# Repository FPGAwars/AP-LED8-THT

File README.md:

# AP-LED8-THT
Alhambra Peripheral board with 8 through-hole LEDs

It is a tiny board with eight 3mm though-hole LEDs for connecting to the Alhambra-II FPGA board.  
This board is also used as a reference for teaching students how to design their first PCB (so, it is a kind of "hello world" hardware)

## Connection to Alhambra II Board

## Certification mark

This board is Opensource hardware, certified by the [OSHWA](https://www.oshwa.org/)

* Certification ID: [ES000043](https://certification.oshwa.org/es000043.html)  

* Certification mark:

## License

Documentation licensed under the [Creative Commons Attribution Share Alike 4.0 International License](https://creativecommons.org/licenses/by-sa/4.0/)

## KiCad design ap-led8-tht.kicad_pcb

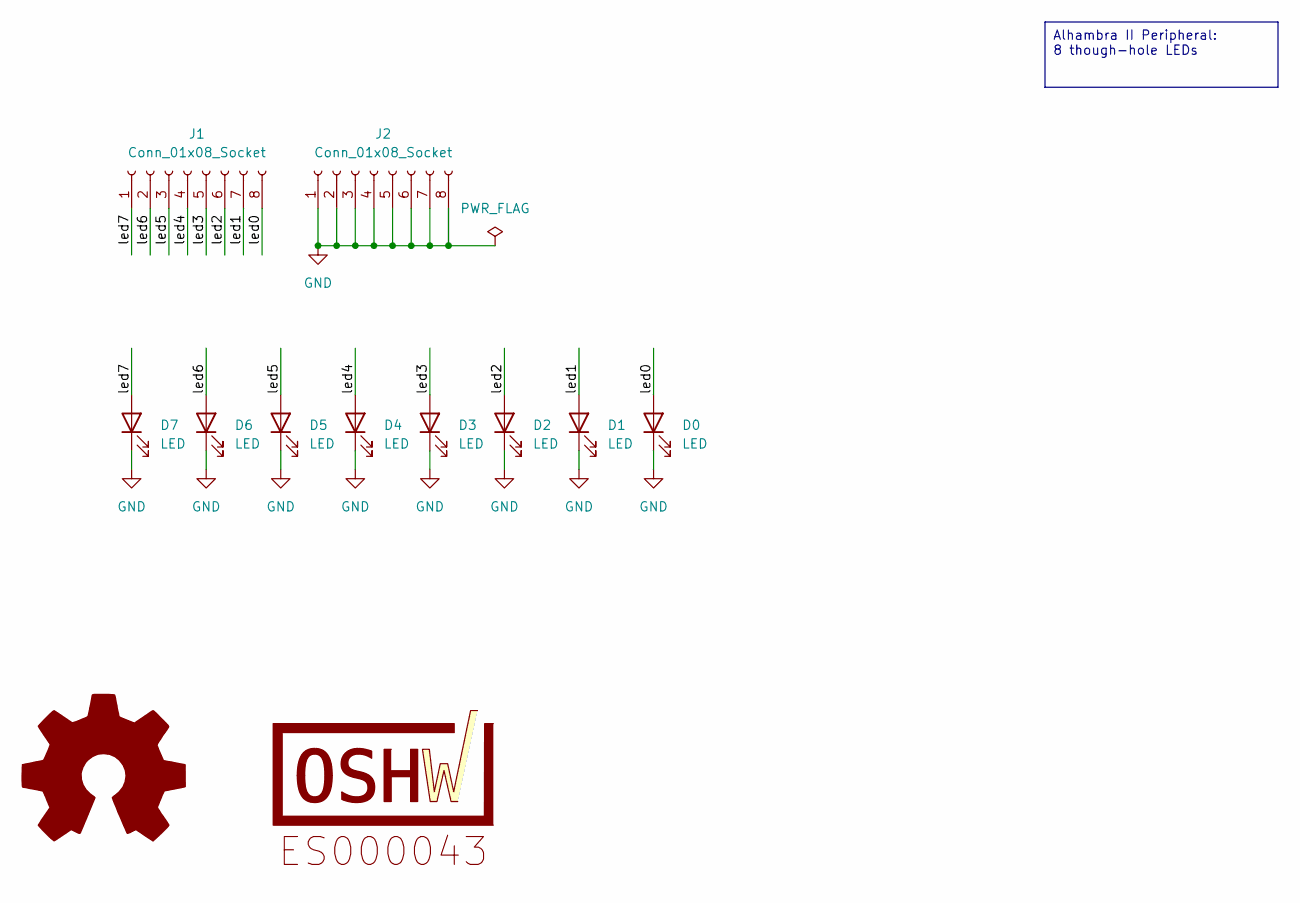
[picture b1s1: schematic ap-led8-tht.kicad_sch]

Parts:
D0, D1, D2, D3, D4, D5, D6, D7: LED; LED_THT__LED_D3.0mm
J1, J2: Conn_01x08_Socket; PinSocket_1x08_P2.54mm_Vertical
LOGO2: (no value)

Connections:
/led0: D0.2 (A), J1.8
/led1: D1.2 (A), J1.7
/led2: D2.2 (A), J1.6
/led3: D3.2 (A), J1.5
/led4: D4.2 (A), J1.4
/led5: D5.2 (A), J1.3
/led6: D6.2 (A), J1.2
/led7: D7.2 (A), J1.1
GND: D0.1 (K), D1.1 (K), D2.1 (K), D3.1 (K), D4.1 (K), D5.1 (K), D6.1 (K), D7.1 (K), J2.1, J2.2, J2.3, J2.4, J2.5, J2.6, J2.7, J2.8

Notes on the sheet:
Alhambra II Peripheral: 8 though-hole LEDs

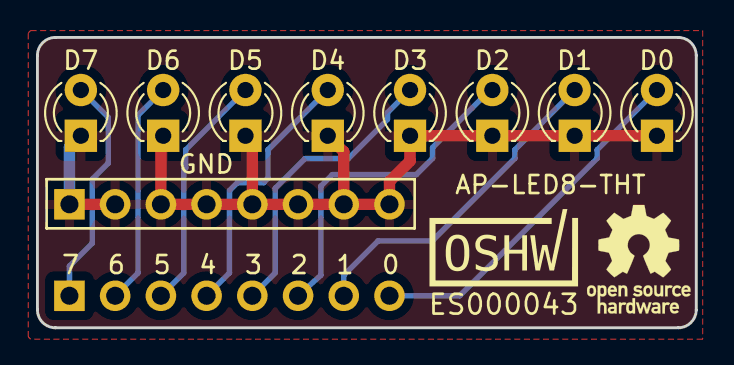
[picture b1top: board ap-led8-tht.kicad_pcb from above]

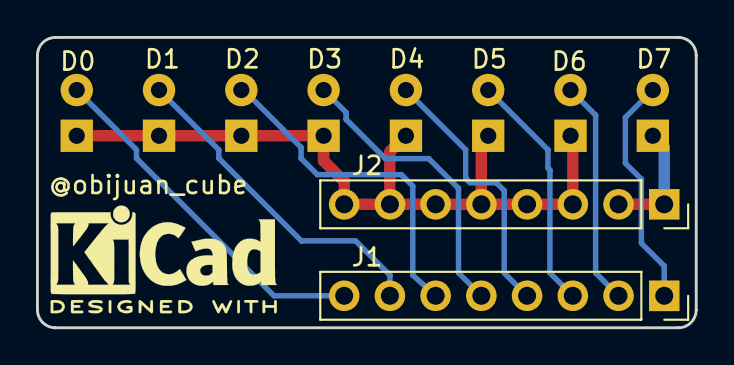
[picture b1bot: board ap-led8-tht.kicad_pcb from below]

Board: 2 copper layers, 36.6 x 16.1 mm, 10 parts (2 on the bottom side), 9 nets.

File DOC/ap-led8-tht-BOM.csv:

"Source:","/home/obijuan/Develop/AP-LED8-THT/ap-led8-tht.kicad_sch"
"Date:","vie 12 ene 2024 10:51:23"
"Tool:","Eeschema 7.0.10-7.0.10~ubuntu22.04.1"
"Generator:","/usr/share/kicad/plugins/bom_csv_grouped_by_value.py"
"Component Count:","10"

"Collated Components:"

"Item","Qty","Reference(s)","Value","LibPart","Footprint","Datasheet","DNP"
"1","8","D0, D1, D2, D3, D4, D5, D6, D7","LED","Device:LED","Monolito:LED_THT__LED_D3.0mm","~",""
"2","2","J1, J2","Conn_01x08_Socket","Connector:Conn_01x08_Socket","Monolito:PinSocket_1x08_P2.54mm_Vertical","~",""

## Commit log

2024-01-11 add initial design
2024-01-11 add monolito footprints and 3dshapes
2024-01-11 Initial PCB
2024-01-11 add top and bottom silkscreens
2024-01-12 Update gitignore
2024-01-12 LEDs moved to make the board less in width
2024-01-12 pcb: update silkscreen
2024-01-12 add license to board and documentation
2024-01-12 Add bom and schematic (in pdf and svg)
2024-01-12 Add interactive bom (ibom)
2024-01-12 add 3D images
2024-01-12 add 3D board images for the documentation
2024-01-12 Add Freecad 3D models
2024-01-12 update pcb
2024-01-12 update pcb: rounded corners
2024-01-12 add Freecad edge
2024-01-15 PCB: add front GND zone
2024-01-15 PCB: fixed DRC warnings
2024-01-15 update Freecad edge
2024-01-15 PCB: New GND zone
2024-01-15 update Freecad 3D
2024-01-19 add cc-by-sa logo
2024-01-19 Add certification UID and mark
2024-01-19 add certification mark footprint
2024-01-19 update freecad 3D model (new top silkscreen)
2024-01-19 add ap-led-tht step
2024-01-19 add Alhambra-II with ap-led-tht 3D Freecad
2024-01-19 update doc images
2024-01-19 schematic: add oshw logo and certification mark
2024-01-19 plot schematic to pdf and svg
2024-01-19 Add manufacturing information
2024-06-29 update files to Kicad 8
